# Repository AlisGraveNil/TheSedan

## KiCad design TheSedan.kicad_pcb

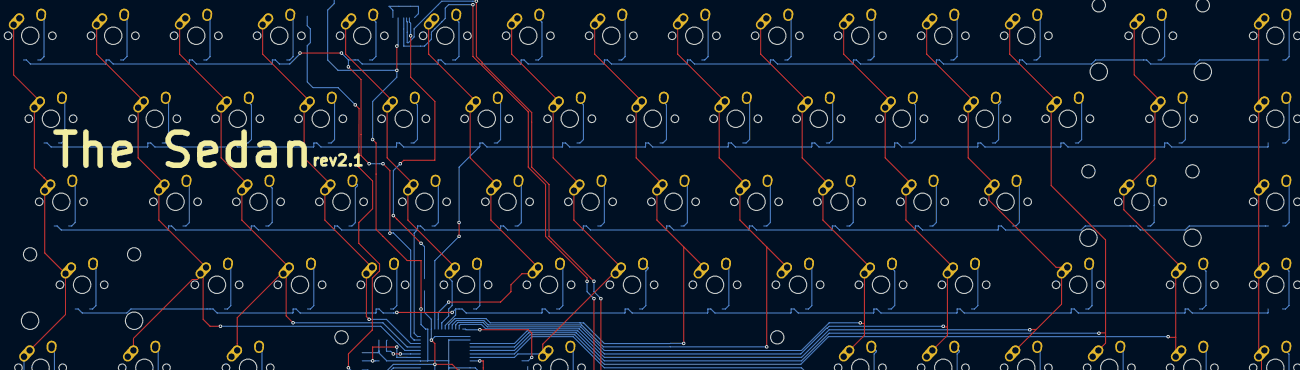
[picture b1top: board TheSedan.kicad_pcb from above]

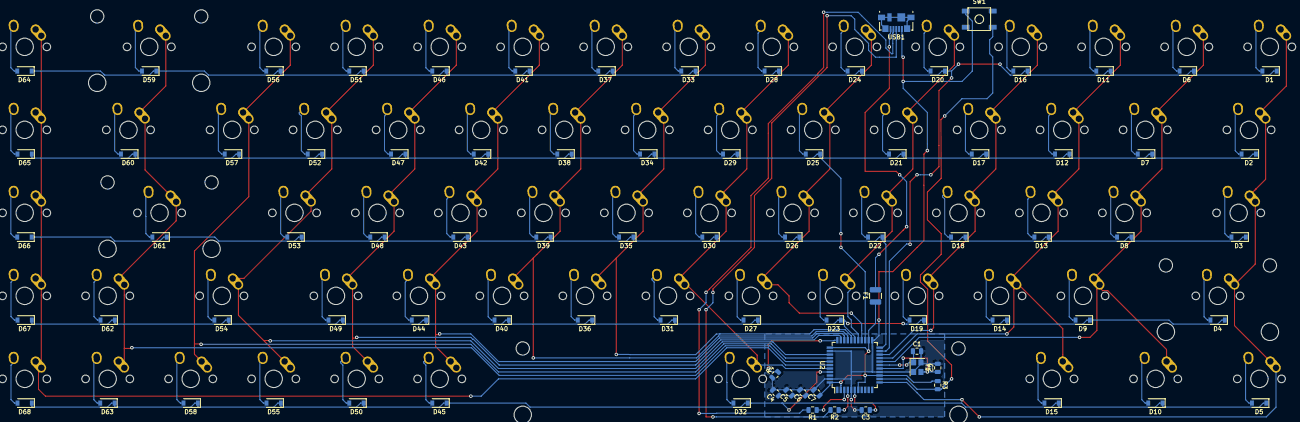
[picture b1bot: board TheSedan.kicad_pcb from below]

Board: 2 copper layers, 152 parts (84 on the bottom side), 100 nets.

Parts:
C1, C2: 22pF; C_0805_2012Metric
C3: 1uF; C_0805_2012Metric
C4, C5, C6: 0.1uF; C_0805_2012Metric
C7: 10uF; C_0805_2012Metric
D1, D2, D3, D4, D5, D6, D7, D8, D9, D10, D11, D12, D13, D14, D15, D16, D17, D18, D19, D20, D21, D22, D23, D24, D25, D26, D27, D28, D29, D30, D31, D32, D33, D34, D35, D36, D37, D38, D39, D40, D41, D42, D43, D44, D45, D46, D47, D48, D49, D50, D51, D52, D53, D54, D55, D56, D57, D58, D59, D60, D61, D62, D63, D64, D65, D66, D67, D68: D_Small; D_SOD-123
F1: 500mA; Fuse_1210_3225Metric
MX1, MX6, MX7, MX8, MX9, MX11, MX12, MX13, MX14, MX16, MX17, MX18, MX19, MX20, MX21, MX22, MX23, MX24, MX25, MX26, MX27, MX28, MX29, MX30, MX31, MX33, MX34, MX35, MX36, MX37, MX38, MX39, MX40, MX41, MX42, MX43, MX44, MX45, MX46, MX47, MX48, MX49, MX50, MX51, MX52, MX53, MX55, MX56, MX57, MX58, MX62, MX63, MX64, MX65, MX66, MX67, MX68: MX-NoLED; MX-1U-NoLED
MX2, MX60: MX-NoLED; MX-1.5U-NoLED
MX3, MX54: MX-NoLED; MX-1.75U-NoLED
MX4, MX61: MX-NoLED; MX-2.25U-NoLED
MX5, MX10, MX15: MX-NoLED; MX-1.25U-NoLED
MX32: MX-NoLED; MX-6.25U-NoLED
MX59: MX-NoLED; MX-2U-NoLED
R1, R2: 22; R_0805_2012Metric
R3, R4: 10k; R_0805_2012Metric
SW1: SW_Push; SKQG-1155865
U2: ATmega32U4-AU; TQFP-44_10x10mm_P0.8mm
USB1: Molex-0548190589; USB_Micro-B_Molex_47346-0001
Y1: 16MHz; Crystal_SMD_3225-4Pin_3.2x2.5mm

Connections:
+5V: C4.1, C5.1, C6.1, C7.1, F1.1, R3.1, U2.2, U2.7, U2.14, U2.24, U2.34, U2.44
D+: R2.2, USB1.3
D-: R1.2, USB1.4
GND: C1.2, C2.2, C3.2, C4.2, C5.2, C6.2, C7.2, R4.1, SW1.1, U2.5, U2.15, U2.23, U2.35, U2.43, USB1.1, Y1.2, Y1.4
unnamed: C1.1, U2.17, Y1.1
unnamed: C2.1, U2.16, Y1.3
unnamed: C3.1, U2.6
unnamed: D1.2, MX1.2
unnamed: D2.2, MX2.2
unnamed: D3.2, MX3.2
unnamed: D4.2, MX4.2
unnamed: D5.2, MX5.2
unnamed: D6.2, MX6.2
unnamed: D7.2, MX7.2
unnamed: D8.2, MX8.2
unnamed: D9.2, MX9.2
unnamed: D10.2, MX10.2
unnamed: D11.2, MX11.2
unnamed: D12.2, MX12.2
unnamed: D13.2, MX13.2
unnamed: D14.2, MX14.2
unnamed: D15.2, MX15.2
unnamed: D16.2, MX16.2
unnamed: D17.2, MX17.2
unnamed: D18.2, MX18.2
unnamed: D19.2, MX19.2
unnamed: D20.2, MX20.2
unnamed: D21.2, MX21.2
unnamed: D22.2, MX22.2
unnamed: D23.2, MX23.2
unnamed: D24.2, MX24.2
unnamed: D25.2, MX25.2
unnamed: D26.2, MX26.2
unnamed: D27.2, MX27.2
unnamed: D28.2, MX28.2
unnamed: D29.2, MX29.2
unnamed: D30.2, MX30.2
unnamed: D31.2, MX31.2
unnamed: D32.2, MX32.2
unnamed: D33.2, MX33.2
unnamed: D34.2, MX34.2
unnamed: D35.2, MX35.2
unnamed: D36.2, MX36.2
unnamed: D37.2, MX37.2
unnamed: D38.2, MX38.2
unnamed: D39.2, MX39.2
unnamed: D40.2, MX40.2
unnamed: D41.2, MX41.2
unnamed: D42.2, MX42.2
unnamed: D43.2, MX43.2
unnamed: D44.2, MX44.2
unnamed: D45.2, MX45.2
unnamed: D46.2, MX46.2
unnamed: D47.2, MX47.2
unnamed: D48.2, MX48.2
unnamed: D49.2, MX49.2
unnamed: D50.2, MX50.2
unnamed: D51.2, MX51.2
unnamed: D52.2, MX52.2
unnamed: D53.2, MX53.2
unnamed: D54.2, MX54.2
unnamed: D55.2, MX55.2
unnamed: D56.2, MX56.2
unnamed: D57.2, MX57.2
unnamed: D58.2, MX58.2
unnamed: D59.2, MX59.2
unnamed: D60.2, MX60.2
unnamed: D61.2, MX61.2
unnamed: D62.2, MX62.2
unnamed: D63.2, MX63.2
unnamed: D64.2, MX64.2
unnamed: D65.2, MX65.2
unnamed: D66.2, MX66.2
unnamed: D67.2, MX67.2
unnamed: D68.2, MX68.2
unnamed: R1.1, U2.3
unnamed: R2.1, U2.4
unnamed: R3.2, SW1.2, U2.13
unnamed: R4.2, U2.33
VCC: F1.2, USB1.5
col0: MX1.1, MX2.1, MX3.1, MX4.1, MX5.1, U2.12
col1: MX6.1, MX7.1, MX8.1, MX9.1, MX10.1, U2.18
col2: MX11.1, MX12.1, MX13.1, MX14.1, MX15.1, U2.19
col3: MX16.1, MX17.1, MX18.1, MX19.1, U2.20
col4: MX20.1, MX21.1, MX22.1, MX23.1, U2.27
col5: MX24.1, MX25.1, MX26.1, MX27.1, U2.26
col6: MX28.1, MX29.1, MX30.1, MX31.1, MX32.1, U2.40
col7: MX33.1, MX34.1, MX35.1, MX36.1, U2.29
col8: MX37.1, MX38.1, MX39.1, MX40.1, U2.30
col9: MX41.1, MX42.1, MX43.1, MX44.1, MX45.1, U2.31
col10: MX46.1, MX47.1, MX48.1, MX49.1, MX50.1, U2.32
col11: MX51.1, MX52.1, MX53.1, MX54.1, MX55.1, U2.36
col12: MX56.1, MX57.1, MX58.1, U2.37
col13: MX59.1, MX60.1, MX61.1, MX62.1, MX63.1, U2.38
col14: MX64.1, MX65.1, MX66.1, MX67.1, MX68.1, U2.39
row0: D1.1, D6.1, D11.1, D16.1, D20.1, D24.1, D28.1, D33.1, D37.1, D41.1, D46.1, D51.1, D56.1, D59.1, D64.1, U2.21
row1: D2.1, D7.1, D12.1, D17.1, D21.1, D25.1, D29.1, D34.1, D38.1, D42.1, D47.1, D52.1, D57.1, D60.1, D65.1, U2.25
row2: D3.1, D8.1, D13.1, D18.1, D22.1, D26.1, D30.1, D35.1, D39.1, D43.1, D48.1, D53.1, D61.1, D66.1, U2.22
row3: D4.1, D9.1, D14.1, D19.1, D23.1, D27.1, D31.1, D36.1, D40.1, D44.1, D49.1, D54.1, D62.1, D67.1, U2.28
row4: D5.1, D10.1, D15.1, D32.1, D45.1, D50.1, D55.1, D58.1, D63.1, D68.1, U2.41

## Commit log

2020-05-02 5/1/20 v2
2020-05-03 5/2/20 v3
2020-05-03 5/2/20 v4
2020-05-04 5/3/20 v1
2020-05-04 5/4/20 v1
2020-05-04 5/4/20 v3
2020-05-05 5/5/20 v1
